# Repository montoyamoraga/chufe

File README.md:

# chufe

## About

chufe is an open source hardware Eurorack power supply by [piruetas](https://piruetas.xyz). It takes 12 V DC from a barrel jack, with reverse polarity protection, and outputs ±12V (from a 20 W isolated DC-DC converter) and +5V (from an L7805 linear regulator) on two 16-pin Eurorack power headers, with an LED for each rail. It is designed to feed a power bus such as [chufebu](https://github.com/piruetasxyz/chufebu). The design is made in KiCad 10 with KiCad's standard libraries plus its own symbol, footprint and 3D model for the DC-DC converter, included in `hardware/bibliotecas/`. Hardware is licensed under CERN-OHL-P-2.0 and documentation under CC-BY-SA-4.0 (see [LICENSE.md](./LICENSE.md)). Documentation, schematic, board render and bill of materials (in Spanish): <https://piruetas.xyz/chufe/>.

## Acerca de

Fuente de alimentación eurorack de [piruetas](https://piruetas.xyz), hecha en KiCad y publicada como hardware de código abierto.

Documentación, esquemático, placa y Bill of materials: <https://piruetas.xyz/chufe/>.

## Características

- Entrada de 12 V DC por jack, con protección contra polaridad inversa.
- Salidas de +12V y -12V desde un convertidor DC-DC aislado de 20 W (URA2412YMD-20WR3).
- Salida de +5V desde un regulador lineal L7805, alimentado desde +12V.
- Dos headers de alimentación Eurorack de 16 pines (2x08), con -12V, GND, +12V y +5V en ambos.
- 4 LEDs indicadores: entrada, -12V, +12V y +5V.
- Placa de 50 × 65 mm, 2 capas, con 4 agujeros de montaje M3.
- Hecha para alimentar un bus como [chufebu](https://github.com/piruetasxyz/chufebu).

## Pines y manual de uso

Los pines de los headers de 16 pines, cómo conectar chufe y las advertencias están en el [manual de uso](https://piruetas.xyz/chufe/#manual-de-uso).

## Revisiones

- `v0.1 rev-a`: fabricada y probada en octubre 2026.
- `v0.1 rev-b`: fabricada y probada en noviembre 2026. Dos headers Eurorack de 16 pines en vez de un header y un conector Molex KK-396, pistas de alimentación más anchas (0.8 mm), C3 cerámico en vez de electrolítico, etiquetas para los LEDs, logo de certificación OSHWA (CL000011) y modelo 3D corregido del convertidor DC-DC.

## Pendiente para rev-1

### Condensadores faltantes

Ahora no hay condensadores en la entrada del convertidor DC-DC ni en sus salidas. rev-a funciona así, pero agregarlos baja el ripple y protege mejor el convertidor:

- Entrada: entre `Net-(D1-K)` (U1 pin 2, después de Q1) y GND. Va después de Q1 para quedar protegido contra polaridad inversa.
- +12V: entre +12V y GND, junto a U1 pin 3.
- -12V: entre -12V y GND, junto a U1 pin 5. Hoy -12V no tiene ningún condensador.

Todos van a GND (que es el mismo nodo que COM y -VIN del convertidor). Cada riel lleva uno de 100 nF lo más cerca posible de los pines de U1, para el ruido de conmutación.

### Sin condensadores electrolíticos

Para que la placa dure más, rev-1 no debería usar condensadores electrolíticos, porque su electrolito líquido se seca con los años. En rev-b C3 ya es cerámico (10 µF / 50 V X5R 1206, LCSC C13585), así que no queda ninguno: los condensadores nuevos también deberían ser cerámicos.

### Materiales sugeridos

- Cerámicos MLCC con dieléctrico X7R: no se secan y son estables con la temperatura. Ojo con la pérdida de capacidad por voltaje DC: un 10 µF / 25 V en 1206 queda en ~4–5 µF a 12 V. Conviene subir el voltaje nominal o el tamaño:
  - Entrada, +12V y -12V: 10 µF / 50 V X7R 1210, más 100 nF en 0805 en cada riel.
  - +5V: C3 ya es 10 µF / 50 V X5R 1206 (C13585) desde rev-b. El L7805 es estable con condensadores cerámicos.
- Los cerámicos no tienen polaridad, así que no hay riesgo de soldar al revés el de -12V.
- Al conectar el jack en caliente, un cerámico solo en la entrada puede generar un pico de voltaje. Dos opciones:
  - Un diodo TVS SMBJ30A (encapsulado SMB) entre `Net-(D1-K)` y GND, que recorta el pico antes del máximo de 36 V del convertidor.
  - Condensadores de polímero sólido en la entrada: no tienen líquido, no se secan y amortiguan mejor que los cerámicos.

## Estructura del repositorio

- [hardware/chufe-v-0-rev-a](./hardware/chufe-v-0-rev-a): proyecto de KiCad (esquemático y placa), los archivos fuente del diseño.
- [hardware/chufe-v-0-rev-a-fab](./hardware/chufe-v-0-rev-a-fab): gerbers y archivos de taladrado para fabricar la placa.
- [hardware/chufe-v-0-rev-a-pcba](./hardware/chufe-v-0-rev-a-pcba): lista de componentes y archivo de posiciones para armado en JLCPCB.
- [hardware/chufe-v-0-rev-b](./hardware/chufe-v-0-rev-b), [hardware/chufe-v-0-rev-b-fab](./hardware/chufe-v-0-rev-b-fab) y [hardware/chufe-v-0-rev-b-pcba](./hardware/chufe-v-0-rev-b-pcba): lo mismo para rev-b.
- [hardware/bibliotecas](./hardware/bibliotecas): símbolo, huella y modelo 3D del convertidor URA2412YMD-20WR3, dibujados por piruetas a partir de la hoja de datos. Van en el repositorio para que el proyecto de KiCad se abra sin instalar bibliotecas adicionales.
- [docs](./docs): documentación, publicada en <https://piruetas.xyz/chufe/>. Las capturas del esquemático y de la placa, y la tabla de Bill of materials, las genera [kicad-retrata](https://github.com/piruetasxyz/kicad-retrata) en cada push (ver [kicad-retrata.yml](./kicad-retrata.yml)).
- [LICENSES](./LICENSES): textos completos de las licencias.

## Fabricación

piruetas vende chufe armado y probado.

Como es hardware de código abierto, los archivos fuente de KiCad, los archivos de fabricación de [hardware/chufe-v-0-rev-b-fab](./hardware/chufe-v-0-rev-b-fab), los de armado de [hardware/chufe-v-0-rev-b-pcba](./hardware/chufe-v-0-rev-b-pcba) y la [Bill of materials](https://piruetas.xyz/chufe/#bill-of-materials-v01-rev-b) están publicados para que cualquiera pueda estudiar, modificar y fabricar el diseño. piruetas no da soporte para unidades fabricadas o armadas por terceros.

## Créditos

- Aarón Montoya-Moraga: investigación, esquemático, PCB, fabricación y documentación.
- Matías Serrano: revisor experto de esquemáticos y PCBs.

## Licencia

chufe es (c) 2026 piruetas SpA / Aarón Montoya-Moraga.

- Hardware (`hardware/`): [CERN-OHL-P-2.0](./LICENSES/CERN-OHL-P-2.0.txt).
- Documentación (`docs/`): [CC-BY-SA-4.0](./LICENSES/CC-BY-SA-4.0.txt).
- El nombre, logo y marca de piruetas no están cubiertos por estas licencias: ver [LicenseRef-piruetas-branding](./LICENSES/LicenseRef-piruetas-branding.txt).

Ver [LICENSE.md](./LICENSE.md) para los detalles. El repositorio sigue la especificación [REUSE](https://reuse.software/).

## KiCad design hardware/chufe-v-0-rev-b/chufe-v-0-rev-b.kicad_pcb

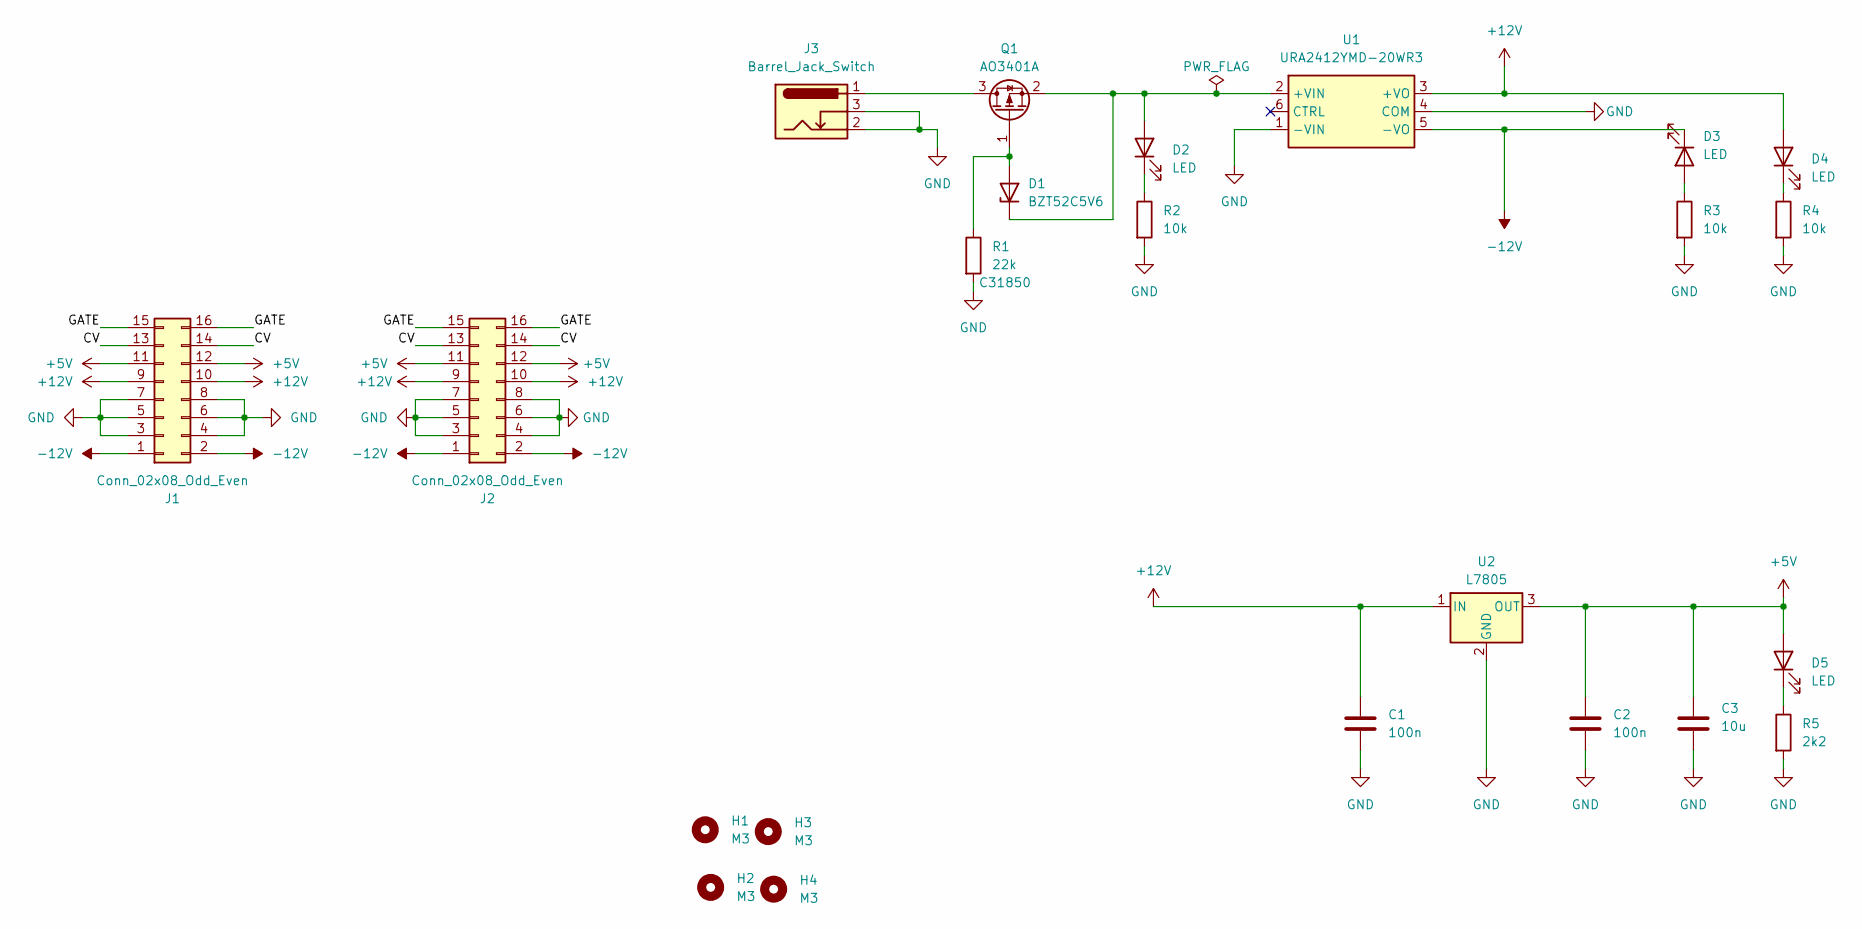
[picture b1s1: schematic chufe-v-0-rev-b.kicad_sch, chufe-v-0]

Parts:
C1, C2: 100n; C_0805_2012Metric; LCSC C49678
C3: 10u; C_1206_3216Metric; LCSC C13585
D1: BZT52C5V6; D_SOD-123; LCSC C19077402
D2, D3, D4, D5: LED; LED_D3.0mm
H1, H2, H3, H4: M3; MountingHole_3.2mm_M3
J1, J2: Conn_02x08_Odd_Even; IDC-Header_2x08_P2.54mm_Vertical
J3: Barrel_Jack_Switch; BarrelJack_Horizontal
Q1: AO3401A; SOT-23; LCSC C15127
R1: 22k; R_0805_2012Metric; LCSC C31850
R2, R3, R4: 10k; R_0805_2012Metric; LCSC C17414
R5: 2k2; R_0805_2012Metric; LCSC C17520
U1: URA2412YMD-20WR3; YLPTEC_URA_YMD-20WR3; MPN URA2412YMD-20WR3; LCSC Part C5369773
U2: L7805; TO-252-2; LCSC C19626525

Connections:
+5V: C2.1, C3.1, D5.2 (A), J1.11, J1.12, J2.11, J2.12, U2.3 (OUT)
+12V: C1.1, D4.2 (A), J1.9, J1.10, J2.9, J2.10, U1.3 (+VO), U2.1 (IN)
-12V: D3.1 (K), J1.1, J1.2, J2.1, J2.2, U1.5 (-VO)
/CV: J1.13, J1.14, J2.13, J2.14
/GATE: J1.15, J1.16, J2.15, J2.16
GND: C1.2, C2.2, C3.2, J1.3, J1.4, J1.5, J1.6, J1.7, J1.8, J2.3, J2.4, J2.5, J2.6, J2.7, J2.8, J3.2, J3.3, R1.2, R2.2, R3.2, R4.2, R5.2, U1.1 (-VIN), U1.4 (COM), U2.2 (GND)
unnamed: D1.2 (A), Q1.1 (G), R1.1
unnamed: D1.1 (K), D2.2 (A), Q1.2 (S), U1.2 (+VIN)
unnamed: D2.1 (K), R2.1
unnamed: D3.2 (A), R3.1
unnamed: D4.1 (K), R4.1
unnamed: D5.1 (K), R5.1
unnamed: J3.1, Q1.3 (D)

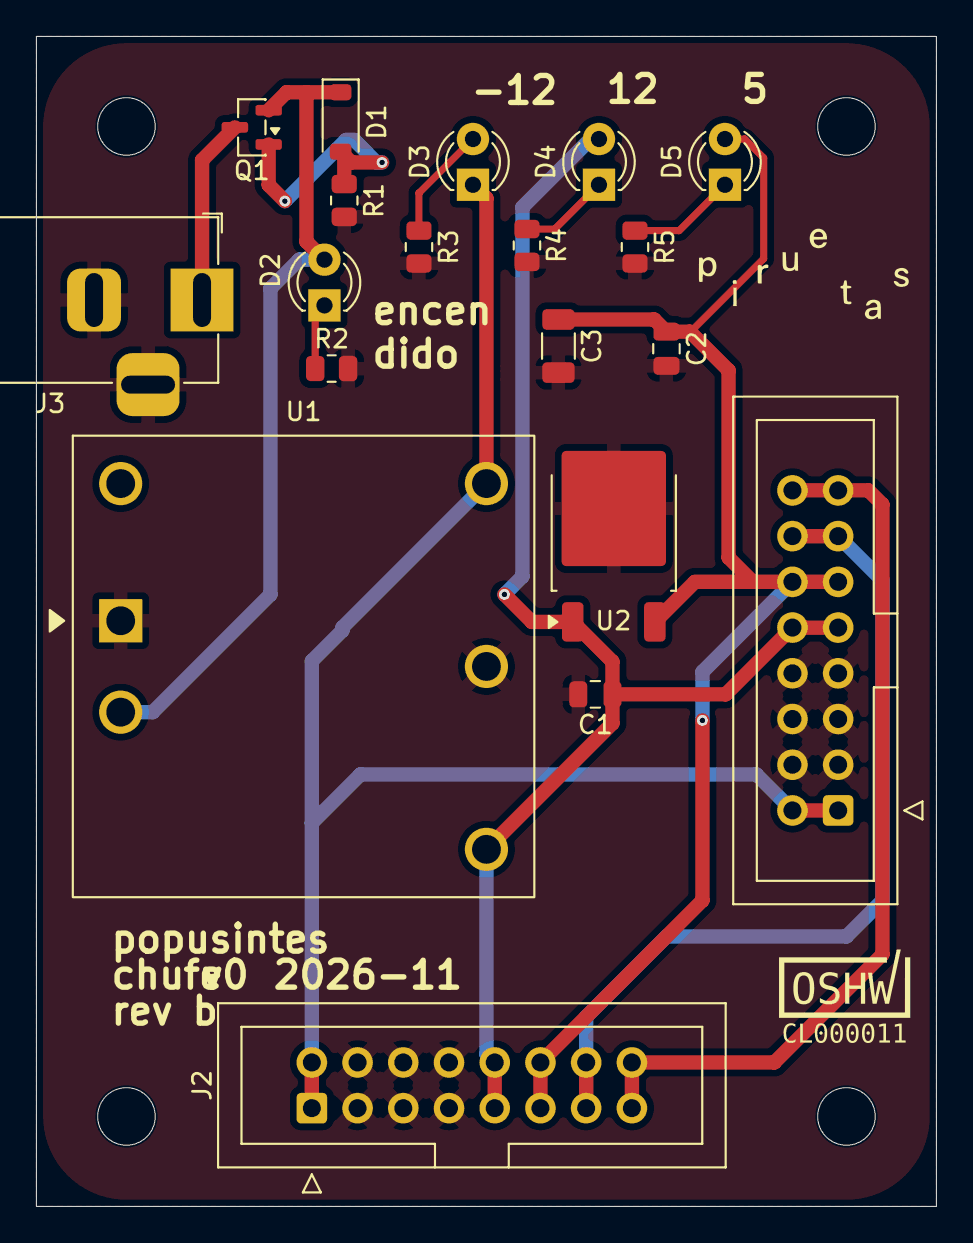
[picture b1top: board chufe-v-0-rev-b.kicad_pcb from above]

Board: 2 copper layers, 50.0 x 65.0 mm, 23 parts (0 on the bottom side), 13 nets.

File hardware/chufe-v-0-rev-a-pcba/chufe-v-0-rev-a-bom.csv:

"Comment","Designator","Footprint","LCSC Part #"
"100n","C1,C2","Capacitor_SMD:C_0805_2012Metric","C49678"
"22u","C3","Capacitor_SMD:CP_Elec_4x5.4","C72502"
"BZT52C5V6","D1","Diode_SMD:D_SOD-123","C19077402"
"AO3401A","Q1","Package_TO_SOT_SMD:SOT-23","C15127"
"22k","R1","Resistor_SMD:R_0805_2012Metric","C31850"
"10k","R2,R3,R4","Resistor_SMD:R_0805_2012Metric","C17414"
"2k2","R5","Resistor_SMD:R_0805_2012Metric","C17520"
"URA2412YMD-20WR3","U1","piruetas:YLPTEC_URA_YMD-20WR3","C5369773"
"L7805","U2","Package_TO_SOT_SMD:TO-252-2","C19626525"
